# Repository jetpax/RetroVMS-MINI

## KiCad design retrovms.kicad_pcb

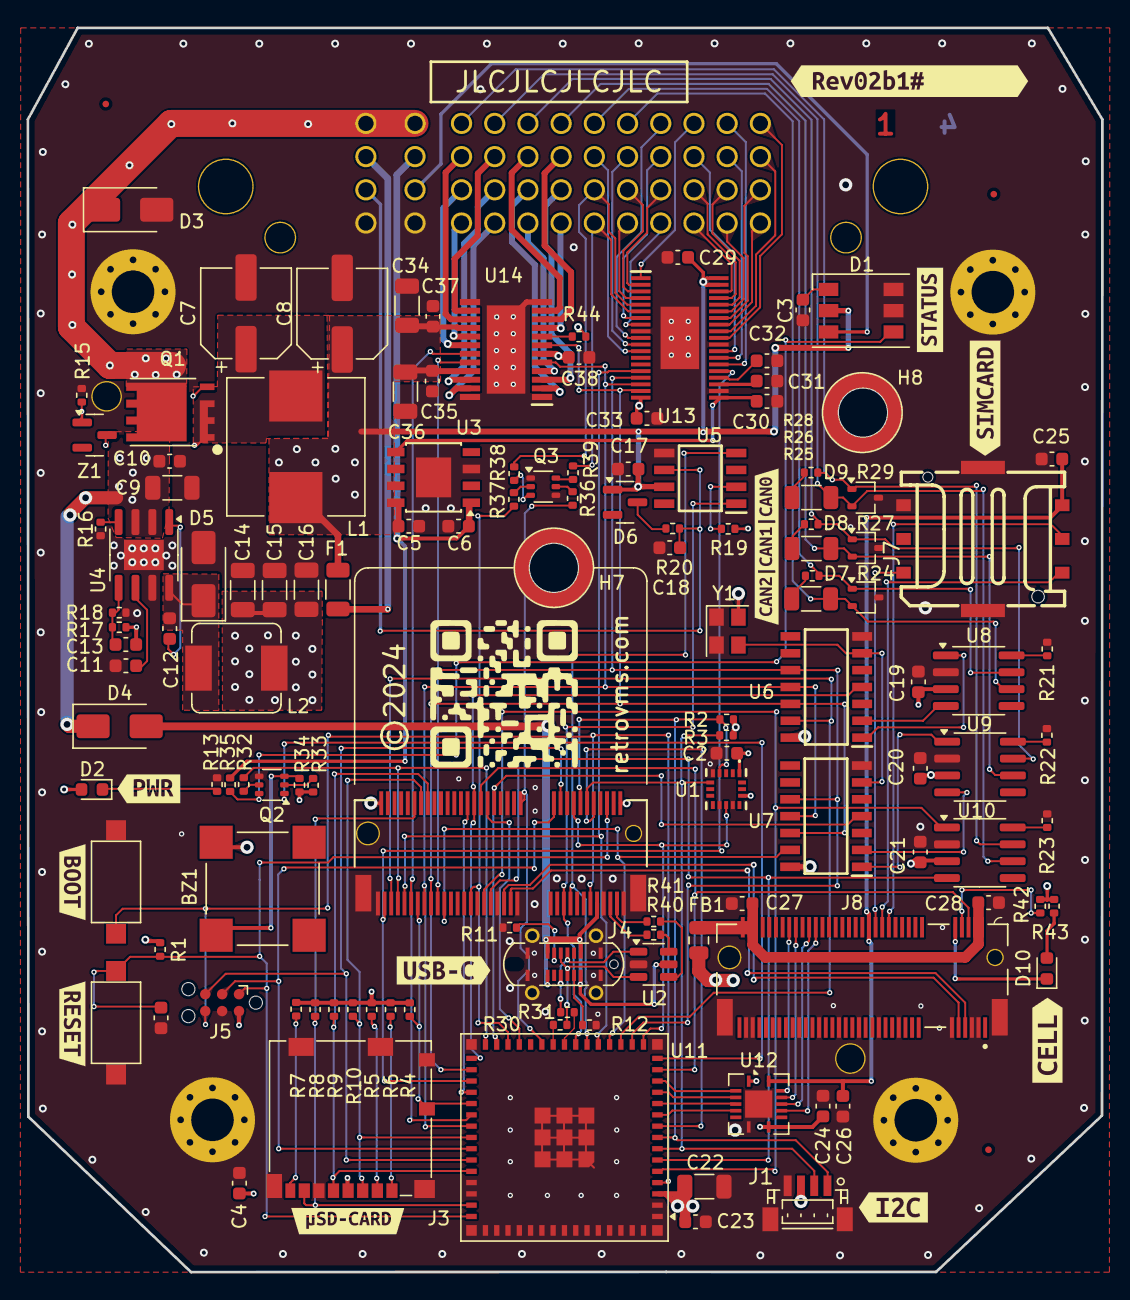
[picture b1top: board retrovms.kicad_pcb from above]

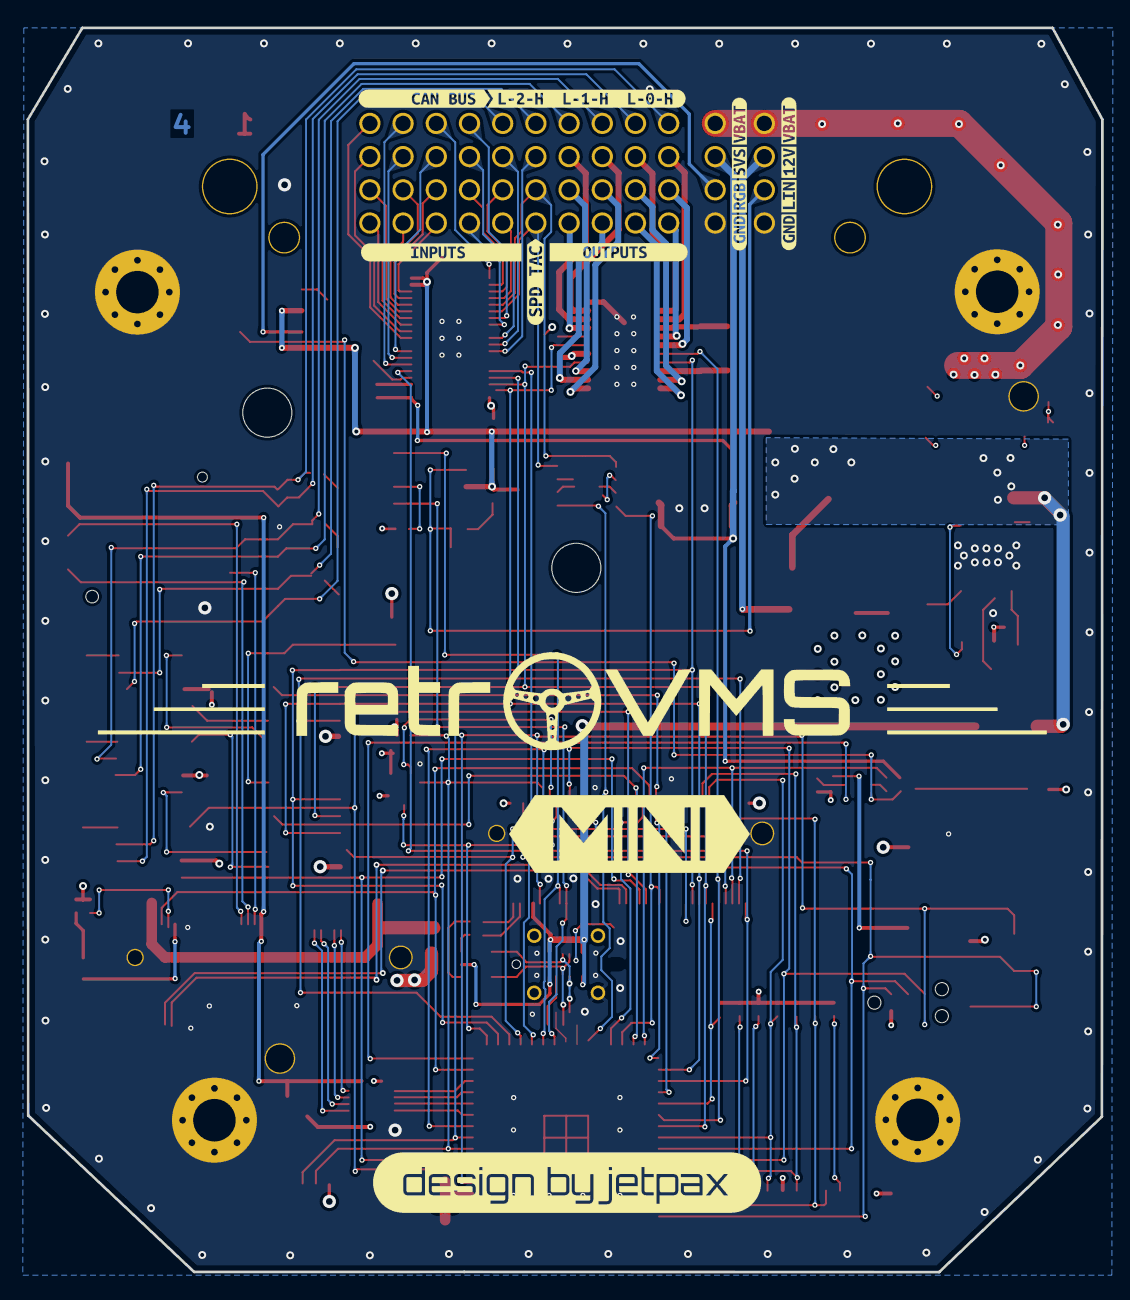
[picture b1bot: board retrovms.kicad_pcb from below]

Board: 4 copper layers, 80.9 x 93.7 mm, 164 parts (15 on the bottom side), 149 nets.

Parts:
BZ1: MLT-8530; PIEZO XDCR_CMT-8503-85B-SMT-TR
C1, C5, C6, C31: 1u; C_0603_1608Metric
C2, C3, C4, C10, C12, C17, C19, C20, C21, C23, C24, C25, C26, C27, C28, C29, C30, C32, C33, C35, C37, C38: 100n; C_0603_1608Metric
C7, C8: 100UF 50V; CP_Elec_6.3x7.7
C9, C34, C36: 4.7u; C_1206_3216Metric
C11: 10n; C_0603_1608Metric
C13, C18: 220p; C_0603_1608Metric
C14, C15, C16, C22: 47u; C_1206_3216Metric
D1: WS2815; LED_WS2812_PLCC6_5.0x5.0mm_P1.6mm
D2, D10: RED_LED; LED_0603_1608Metric
D3: 36V; D_SMA
D4, D5: SS54; D_SMA
D6: BAV70; SOT-23
D7, D8, D9: PESD1CAN-UX; SOT-323_SC-70
F1: 300mA; R_1206_3216Metric
FB1: FerriteBead; C_0805_2012Metric
FID1, FID2, FID3: Fiducial; Fiducial_0.5mm_Mask1mm
H1, H3, H4, H6: MountingHole; MountingHole_3.2mm_M3_Pad_Via
H2, H5: Locating Hole; PTH MountingHole_2.1mm
H7: M2.5 x 1.5mm; WURTH 2.5mm standoff WE_9774025151R
H8: M2.5x3mm; 2.5mmx3mm standoff
J1: JST_PH/STEMMA QT; CONN-SMD_BM04B-SRSS-TB
J2: molex_48pin_500762-0481; Molex_48_MRE
J3: Micro_SD_Card_Det; microSD_HC_Molex_104031-0811
J4: USB_C_Receptacle_USB2.0; USB-C-SMD_GT-USB-7055E
J5: TC2030-IDC_ESP; Tag-Connect_TC2030-IDC-NL_2x03_P1.27mm_Vertical
J6: MicroMod Processor Socket
J7: nanoSIM socket; nanoSIM_SNO-1304-T
J8: M.2 B-key socket; B-Key SIM7600
L1: 1.2u; L_Wuerth_HCI-1050
L2: 1u5 9A 9mΩ; L_Sumida_CDMC6D28_7.25x6.5mm
NT1, NT2: NetTie_2; NetTie-2_SMD_Pad0.15mm
Q1: HY15P03C2; POWERTDFN-8
Q2, Q3: MMDT3904; SOT-363_SC-70-6
R1: 10K; R_0402_1005Metric
R2, R3, R11, R12, R35: 5K1; R_0402_1005Metric
R4, R5, R6, R7, R8, R9, R10, R15, R19, R44: 10k; R_0402_1005Metric
R13, R20, R32, R33, R34, R42: 1K; R_0402_1005Metric
R16: 18k; R_0402_1005Metric
R17: 100k; R_0402_1005Metric
R18: 28k; R_0402_1005Metric
R21, R22, R23, R36, R37, R43: 100K; R_0402_1005Metric
R24, R26, R28, R30, R31, R40, R41: 0R; R_0402_1005Metric
R25, R27, R29: 120R 0.25W; R_1206_3216Metric
R38, R39: 100R; R_0402_1005Metric
SW1, SW2: SW_Push; SW_SPST_CK_RS282G05A3
U1: LIS3DHTR
U2: USBLC6-2SC6; SOT-23-6
U3: TLS115B0EJXUMA1; Infineon_PG-DSO-8-43
U4: LMR14030; SOIC-8-1EP_3.9x4.9mm_P1.27mm_EP2.29x3mm
U5: TLIN2027DRQ1; SOIC127P600X175-8N
U6, U7: MCP2518FDT-E_SL; SOIC127P600X175-14N
U8, U9, U10: SN65HVD230; SOIC-8_3.9x4.9mm_P1.27mm
U11: ESP32-S3-MINI-1-N4R2; ESP32-S2-MINI-1U
U12: TXB0104RGY; Texas_S-PVQFN-N14
U13: TIC10024QDCPRQ1; SOP50P640X120-39N
U14: TLE94112; SOP65P600X170-25N
Y1: 40MHz; Oscillator_SMD_Abracon_ASE-4Pin_3.2x2.5mm
Z1: BZX84C10; SOT-23
kibuzzard-65E9ED88: G***; kibuzzard-65E9ED88
kibuzzard-65E9EDFE: G***; kibuzzard-65E9EDFE
kibuzzard-65E9EE5D: G***; kibuzzard-65E9EE5D
kibuzzard-65E9F7F5: G***; kibuzzard-65E9F7F5
kibuzzard-65E95F8C: G***; kibuzzard-65E95F8C
kibuzzard-65E965A2: G***; kibuzzard-65E965A2
kibuzzard-65E9621C: G***; kibuzzard-65E9621C
kibuzzard-65E96189, kibuzzard-65E96189#2: G***; kibuzzard-65E96189
kibuzzard-65E96414, kibuzzard-65E96414#2: G***; kibuzzard-65E96414
kibuzzard-65E96519: G***; kibuzzard-65E96519
kibuzzard-65E96540: G***; kibuzzard-65E96540
kibuzzard-65EA014A: G***; kibuzzard-65EA014A
kibuzzard-65EA0126: G***; kibuzzard-65EA0126
kibuzzard-65ECBD98: G***; kibuzzard-65ECBD98
kibuzzard-65ECBDEA: G***; kibuzzard-65ECBDEA
kibuzzard-65ECCF8C: G***; kibuzzard-65ECCF8C
kibuzzard-65ECCF47: G***; kibuzzard-65ECCF47
kibuzzard-65ECCF95: G***; kibuzzard-65ECCF95
kibuzzard-65F0D2D4: G***; kibuzzard-65F0D2D4
kibuzzard-65F0D04E: G***; kibuzzard-65F0D04E
kibuzzard-65F0D511: G***; kibuzzard-65F0D511
kibuzzard-65F06A8F: G***; kibuzzard-65F06A8F
kibuzzard-65F084C8: G***; kibuzzard-65F084C8
kibuzzard-65F24715: G***; kibuzzard-65F24715

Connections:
/BUZZ: J6.69 (G7), R32.2, U11.30 (IO48)
/Bus Transceivers/CAN0_H: D9.1 (C1), J2.9, R28.2, U10.7 (CANH)
/Bus Transceivers/CAN0_L: D9.2 (C2), J2.13, R29.2, U10.6 (CANL)
/Bus Transceivers/CAN1_H: D8.1 (C1), J2.17, R26.2, U9.7 (CANH)
/Bus Transceivers/CAN1_L: D8.2 (C2), J2.21, R27.1, U9.6 (CANL)
/Bus Transceivers/CAN2_H: D7.1 (C1), J2.25, R24.2, U8.7 (CANH)
/Bus Transceivers/CAN2_L: D7.2 (C2), J2.29, R25.1, U8.6 (CANL)
/Bus Transceivers/CAN_CLK: U6.6 (OSC1), U7.6 (OSC1), Y1.3 (Out)
/CAN0_RX: J6.41 (CAN_RX), U10.4 (R), U11.6 (IO2)
/CAN0_TX: J6.43 (CAN_TX), U10.1 (D), U11.5 (IO1)
/CAN1_CS: J6.55 (SPI_CS), U7.13 (NCS), U11.19 (IO15)
/CAN1_INT: J6.40 (G0), U7.4 (~INT), U11.29 (IO34)
/CAN2_CS: J6.71 (G6), U6.13 (NCS), U11.18 (IO14)
/CAN2_INT: J6.46 (G3), U6.4 (~INT), U11.31 (IO35)
/D+: J4.A6 (D+), J4.B6 (D+), R31.1, U2.3 (I/O2)
/D-: J4.A7 (D-), J4.B7 (D-), R30.2, U2.1 (I/O1)
/DEV_D+: R41.2, U2.4 (I/O2)
/DEV_D-: R40.2, U2.6 (I/O1)
/FREQ0: J6.47 (PWM1), R37.2, U11.28 (IO33)
/FREQ1: J6.32 (PWM0), R36.2, U11.25 (IO21)
/GD0: J6.10 (D0), U11.9 (IO5)
/I2C_INT: J6.16 (I2C_INT), U1.11 (INT1), U11.16 (IO12)
/INP_CS: J6.67 (G8), U11.20 (IO16), U13.15 (~CS)
/INP_INT: J6.73 (G5), U11.33 (IO37), U13.24 (~INT)
/IPC_CS: J6.42 (G1), U11.27 (IO47)
/IPC_INT: J6.48 (G4), U11.34 (IO38)
/Inputs/IN2: J2.41, U13.25 (IN2)
/Inputs/IN3: J2.42, U13.26 (IN3)
/Inputs/IN4: J2.38, U13.27 (IN4)
/Inputs/IN5: J2.45, U13.29 (IN5)
/Inputs/IN6: J2.46, U13.30 (IN6)
/Inputs/IN7: J2.48, U13.31 (IN7)
/Inputs/IN8: J2.47, U13.32 (IN8)
/Inputs/IN9: J2.44, U13.33 (IN9)
/Inputs/IN10: J2.43, U13.34 (IN10)
/Inputs/IN11: J2.39, U13.35 (IN11)
/Inputs/IN12: J2.40, U13.36 (IN12)
/Inputs/IN13: J2.37, U13.1 (IN13)
/Inputs/IN14: J2.35, U13.2 (IN14)
/Inputs/IN15: J2.31, U13.3 (IN15)
/Inputs/IN16: J2.32, U13.4 (IN16)
/Inputs/IN17: J2.27, NT1.2, U13.5 (IN17)
/Inputs/IN18: J2.28, NT2.2, U13.6 (IN18)
/Inputs/IN19: J2.34, U13.7 (IN19)
/Inputs/IN20: J2.36, U13.8 (IN20)
/Inputs/IN21: J2.33, U13.10 (IN21)
/Inputs/IN22: J2.30, U13.11 (IN22)
/Inputs/IN23: J2.26, U13.12 (IN23)
/LED_STRIP: D1.3 (DOUT), J2.7
/LINBUS: C18.1, J2.3, R20.1, U5.6 (LIN)
/LIN_RX: J6.19 (RX1), U5.1 (RXD), U11.22 (IO18)
/LIN_TX: J6.17 (TX1), U5.4 (TXD), U11.21 (IO17)
/MDM_D+: J6.35 (D+), J8.7
/MDM_D-: J6.37 (D-), J8.9
/MDM_DTR: U11.10 (IO6), U12.5 (A4)
/MDM_PWR: J6.44 (G2), J8.6, U11.14 (IO10)
/MDM_RTS: U11.11 (IO7), U12.4 (A3)
/MDM_RX: U11.12 (IO8), U12.3 (A2)
/MDM_TX: U11.13 (IO9), U12.2 (A1)
/MISO: J6.59 (SPI_SDO), U6.12 (SDO), U7.12 (SDO), U11.32 (IO36), U13.18 (SO), U14.7 (SDO)
/MOSI: J6.61 (SPI_SDI), U6.11 (SDI), U7.11 (SDI), U11.37 (IO41), U13.17 (SI), U14.5 (SDI)
/OUT_CS: J6.65 (G9_ADCD-), U11.36 (IO40), U14.19 (CSN)
/Outputs/OUT1: J2.19 (OUT1), U14.2 (OUT1)
/Outputs/OUT2: J2.16 (OUT2), U14.23 (OUT2)
/Outputs/OUT3: J2.14 (OUT3), U14.14 (OUT3)
/Outputs/OUT4: J2.18 (OUT4), U14.11 (OUT4)
/Outputs/OUT5: J2.23 (OUT5), U14.3 (OUT5)
/Outputs/OUT6: J2.22 (OUT6), U14.10 (OUT6)
/Outputs/OUT7: J2.20 (OUT7), U14.4 (OUT7)
/Outputs/OUT8: J2.15 (OUT8), U14.22 (OUT8)
/Outputs/OUT9: J2.24 (OUT9), U14.9 (OUT9)
/Outputs/OUT10: J2.10 (OUT10), U14.15 (OUT10)
/Outputs/OUT11: J2.12 (OUT11), U14.17 (OUT11)
/Outputs/OUT12: J2.11 (OUT12), U14.18 (OUT12)
/Power/SW: C12.1, D5.1 (K), L2.1, U4.8 (SW)
/Power/V+: C7.1, L1.1, Q1.S, Z1.3 (K)
/Processor/M.2 WWAN Socket/MDM_VBAT: C27.1, C28.1, FB1.2, J8.2, J8.4, J8.70, J8.72, J8.74
/Processor/M.2 WWAN Socket/SIM_CLK: J7.C3 (CLK), J8.32
/Processor/M.2 WWAN Socket/SIM_IO: J7.C7 (I/O), J8.34
/Processor/M.2 WWAN Socket/SIM_RST: J7.C2 (RST), J8.30
/Processor/M.2 WWAN Socket/SIM_VCC: C25.1, C26.1, J7.C1 (VCC), J8.36, U12.14 (VCCB)
/Processor/M.2 WWAN Socket/W_DISABLE: J8.8, R43.2
/Processor/PIEZO: BZ1.N, Q2.3 (C2), R34.1
/Processor/RGB_LED: D1.4 (DIN), Q2.6 (C1), R35.1
/Processor/RMTLED: Q2.1 (E1), U11.15 (IO11)
/Processor/SPEEDO: NT2.1, R39.1
/Processor/TACHO: NT1.1, R38.1
/Processor/USB_D+: R31.2, U11.24 (IO20)
/Processor/USB_D-: R30.1, U11.23 (IO19)
/RXD0: J5.5 (RX), J6.20 (RX2), U11.40 (RXD0)
/SCL: J1.1, J6.14 (I2C_SCL), R2.1, U1.4 (SCL/SCK), U11.8 (IO4)
/SCLK: J6.57 (SPI_SCK), U6.10 (SCK), U7.10 (SCK), U11.17 (IO13), U13.16 (SCLK), U14.20 (SCLK)
/SDA: J1.2, J6.12 (I2C_SDA), R3.1, U1.6 (SDA/SDI), U11.7 (IO3)
/SD_CLK: J3.5 (CLK), J6.60 (SDIO_CLK), R9.2, U11.41 (IO45)
/SD_CMD: J3.3 (CMD), J6.62 (SDIO_CMD), R10.2, U11.38 (IO42)
/SD_DAT0: J3.7 (DAT0), J6.64 (SDIO_DATA0), R8.2, U11.44 (IO46)
/SD_DAT1: J3.8 (DAT1), R7.2
/SD_DAT2: J3.1 (DAT2), R6.2
/SD_DAT3: J3.2 (DAT3/CD), R5.2
/SD_DET: J3.9 (DET), J6.63 (G10_ADCD+), R4.2, U11.35 (IO39)
/TXD0: J5.3 (TX), J6.22 (TX2), U11.39 (TXD0)
/~BOOT: J5.6 (IO0), J6.11 (~BOOT), SW2.2, U11.4 (IO0)
/~RESET: C1.1, J5.1 (EN), J6.6 (~RESET), R1.1, SW1.2, U11.45 (EN)
AREF: C30.1, U3.5 (ADJ), U13.20 (CAP_A)
GND: C1.2, C2.2, C3.2, C4.2, C5.2, C6.2, C7.2, C8.2, C9.2, C10.2, C11.2, C14.2, C15.2, C16.2, C17.2, C18.2, C19.2, C20.2, C21.2, C22.2, C23.2, C24.2, C25.2, C26.2, C27.2, C28.2, C29.2, C30.2, C31.2, C32.2, C33.2, C34.2, C35.2, C36.2, C37.2, C38.2, D1.5 (GND), D1.6 (BIN), D3.2 (A2), D5.2 (A), D7.3 (C3), D8.3 (C3), D9.3 (C3), H1.1, H2.1, H3.1, H4.1, H5.1, H6.1, H7.1, H8.1, J1.4, J1.MP (MountPin), J2.4, J2.8, J3.6 (VSS), J3.10 (DET_A), J3.11 (SHIELD), J4.A1 (GND), J4.A12 (GND), J4.B1 (GND), J4.B12 (GND), J4.S1 (SHIELD), J5.4 (GND), J6.1 (GND), J6.7 (GND), J6.33 (GND), J6.36 (GND), J6.39 (GND), J6.45 (GND), J6.75 (GND), J6.H1 (HOLE), J6.H2 (HOLE), J6.S1 (SHIELD), J6.S2 (SHIELD), J7.C5 (GND), J7.S1 (GND), J8.3, J8.5, J8.11, J8.27, J8.33, J8.39, J8.45, J8.51, J8.57, J8.71, J8.73, J8.H1 (HOLE), J8.H2 (HOLE), J8.S1 (SHIELD), J8.S2 (SHIELD), Q2.4 (E2), Q3.1 (E1), Q3.4 (E2), R11.1, R12.1, R13.1, R15.2, R16.2, R18.2, R21.1, R22.1, R23.1, SW1.1, SW2.1, U1.5 (GND), U1.10 (RES), U1.12 (GND), U2.2 (GND), U3.3 (GND), U3.9 (GND), U4.7 (GND), U4.9 (GND), U5.5 (GND), U6.7 (VSS), U7.7 (VSS), U8.2 (GND), U9.2 (GND), U10.2 (GND), U11.1 (GND), U11.2 (GND), U11.42 (GND), U11.43 (GND), U11.46 (GND), U11.47 (GND), U11.48 (GND), U11.49 (GND), U11.50 (GND), U11.51 (GND), U11.52 (GND), U11.53 (GND), U11.54 (GND), U11.55 (GND), U11.56 (GND), U11.57 (GND), U11.58 (GND), U11.59 (GND), U11.60 (GND), U11.61 (GND), U11.62 (GND), U11.63 (GND), U11.64 (GND), U11.65 (GND), U12.7 (GND), U12.15 (Pad), U13.9 (AGND), U13.21 (RESET), U13.28 (DGND), U13.39 (EP), U14.1 (GND), U14.12 (GND), U14.13 (GND), U14.24 (GND), U14.25 (EDP), Y1.1 (Standby), Y1.2 (GND)
unnamed: C3.1, D1.1 (VCC)
unnamed: D2.1 (K), R13.2
unnamed: D6.3 (K), R20.2
unnamed: D10.2 (A), R42.2
unnamed: D10.1 (K), J8.10
unnamed: J4.A5 (CC1), R12.2
unnamed: J4.B5 (CC2), R11.2
unnamed: J6.3 (D+), R41.1
unnamed: J6.5 (D-), R40.1
unnamed: Q2.2 (B1), R33.1
unnamed: Q2.5 (B2), R32.1
unnamed: Q3.2 (B1), R37.1
unnamed: Q3.6 (C1), R39.2
unnamed: Q3.5 (B2), R36.1
unnamed: Q3.3 (C2), R38.2
unnamed: R24.1, R25.2
unnamed: R26.1, R27.2
unnamed: R28.1, R29.1
unnamed: C12.2, U4.1 (BOOT)
unnamed: C13.2, R17.1, R18.1, U4.5 (FB)
unnamed: R16.1, U4.4 (RT)
unnamed: C11.1, U4.6 (SS)
unnamed: R19.2, U5.2 (EN)
unnamed: U6.2 (RXCAN), U8.4 (R)
unnamed: U6.1 (TXCAN), U8.1 (D)
unnamed: U7.2 (RXCAN), U9.4 (R)
unnamed: U7.1 (TXCAN), U9.1 (D)
unnamed: R21.2, U8.8 (Rs)
unnamed: R22.2, U9.8 (Rs)
unnamed: R23.2, U10.8 (Rs)
unnamed: J8.60, U12.13 (B1)
unnamed: J8.58, U12.12 (B2)
unnamed: J8.54, U12.11 (B3)
unnamed: J8.52, U12.10 (B4)
unnamed: C32.1, U13.23 (CAP_D)
unnamed: C31.1, U13.22 (CAP_PRE)
unnamed: R44.2, U14.8 (EN)
unnamed: Q1.G, R15.1, Z1.1 (A)
SENSOR_5V: C6.1, J2.6, R35.2, U3.1 (OUT)
SENSOR_12V: F1.2, J2.2
VBAT: D3.1 (A1), J2.1, J2.5, Q1.D
VBUS: D4.2 (A), J4.A4 (VBUS), J4.A9 (VBUS), J4.B4 (VBUS), J4.B9 (VBUS), J6.9 (VUSB), U2.5 (VBUS)
VDD: BZ1.P, C2.1, C4.1, C13.1, C14.1, C15.1, C16.1, C19.1, C20.1, C21.1, C22.1, C23.1, C24.1, C33.1, C38.1, D2.2 (A), FB1.1, J1.3, J3.4 (VDD), J5.2 (VDD), J6.2 (3.3V), J6.74 (3.3V), L2.2, R1.2, R2.2, R3.2, R4.1, R5.1, R6.1, R7.1, R8.1, R9.1, R10.1, R17.2, R19.1, R33.2, R34.2, R42.1, R43.1, R44.1, U1.1 (VDDIO), U1.14 (VDD), U6.14 (VDD), U7.14 (VDD), U8.3 (VCC), U9.3 (VCC), U10.3 (VCC), U11.3 (3V3), U12.1 (VCCA), U12.8 (OE), U13.19 (VDD), U14.6 (VDD), Y1.4 (VDD)
VPROT: C5.1, C8.1, C9.1, C10.1, C17.1, C29.1, C34.1, C35.1, C36.1, C37.1, D1.2 (VDD), D4.1 (K), D6.1 (A), F1.1, L1.2, U3.7 (EN), U3.8 (IN), U4.2 (VIN), U4.3 (EN), U5.7 (VSUP), U13.37 (VS_1), U13.38 (VS_2), U14.16 (VS1), U14.21 (VS2)

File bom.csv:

Designator,Footprint,Quantity,Value,LCSC Part #
BZ1,PIEZO XDCR_CMT-8503-85B-SMT-TR,1,MLT-8530,C94599
"C1, C31, C5, C6",0603,4,1u,C15849
"C10, C12, C17, C19, C2, C20, C21, C23, C24, C25, C26, C27, C28, C29, C3, C30, C32, C33, C35, C37, C38, C4",0603,22,100n,C14663
C11,0603,1,10n,C57112
"C13, C18",0603,2,220p,C1603
"C14, C15, C16, C22",1206,4,47u,C96123
"C34, C36, C9",1206,3,4.7u,C29823
"C7, C8",CP_Elec_6.3x7.7,2,100UF 50V,C7461243
D1,LED_WS2812_PLCC6_5.0x5.0mm_P1.6mm,1,WS2815,C4154879
"D10, D2",0603,2,RED_LED,C965799
D3,D_SMA,1,36V,C83266
"D4, D5",D_SMA,2,SS54,C22452
D6,SOT-23,1,BAV70,C68978
"D7, D8, D9",SOT-323_SC-70,3,PESD1CAN-UX,C907839
F1,1206,1,300mA,C207035
FB1,0805,1,FerriteBead,C16903
H7,WURTH 2.5mm standoff WE_9774025151R,1,M2.5 x 1.5mm,C2915629
H8,2.5mmx3mm standoff,1,M2.5x3mm,C2916380
J1,CONN-SMD_BM04B-SRSS-TB,1,JST_PH/STEMMA QT,C160390
J3,microSD_HC_Molex_104031-0811,1,Micro_SD_Card_Det,C585350
J4,USB-C-SMD_GT-USB-7055E,1,USB_C_Receptacle_USB2.0,C7450622
J6,MicroMod Processor Socket,1,MicroMod Processor Socket,C841649
J7,nanoSIM_SNO-1304-T,1,nanoSIM socket,C428460
J8,B-Key SIM7600,1,M.2 B-key socket,C2761526
L1,L_Wuerth_HCI-1050,1,1.2u,C149536
L2,L_Sumida_CDMC6D28_7.25x6.5mm,1, 1u5 9A 9mΩ,C216162
Q1,POWERTDFN-8,1,HY15P03C2,C123687
"Q2, Q3",SOT-363_SC-70-6,2,MMDT3904,C3018510
"R1, R10, R15, R19, R4, R44, R5, R6, R7, R8, R9",0402,11,10K,C25744
"R11, R12, R2, R3, R35",0402,5,5K1,C25905
"R13, R20, R32, R33, R34, R42",0402,6,1K,C11702
R16,0402,1,18k,C25762
"R17, R21, R22, R23, R36, R37, R43",0402,7,100k,C25741
R18,0402,1,28k,C25772
"R24, R26, R28, R30, R31",0402,5,0R,C17168
"R25, R27, R29",1206,3,120R 0.25W,C17909
"R38, R39",0402,2,100R,C25076
"SW1, SW2",SW_SPST_CK_RS282G05A3,2,SW_Push,C398054
U1,LIS3DHTR,1,LIS3DHTR,C15134
"U10, U8, U9",SOIC-8_3.9x4.9mm_P1.27mm,3,SN65HVD230,C12084
U11,ESP32-S2-MINI-1U,1,ESP32-S3-MINI-1-N4R2,C3013941 
U12,Texas_S-PVQFN-N14,1,TXB0104RGY, C400708
U13,SOP50P640X120-39N,1,TIC10024QDCPRQ1,C2652907
U14,SOP65P600X170-25N,1,TLE94112,C2680272 
U2,SOT-23-6,1,USBLC6-2SC6,C7519
U3,Infineon_PG-DSO-8-43,1,TLS115B0EJXUMA1,C3743696
U4,SOIC-8-1EP_3.9x4.9mm_P1.27mm_EP2.29x3mm,1,LMR14030,C182078
U5,SOIC127P600X175-8N,1,TLIN2027DRQ1,C2862879
"U6, U7",SOIC127P600X175-14N,2,MCP2518FDT-E_SL,C626759
Y1,Oscillator_SMD_Abracon_ASE-4Pin_3.2x2.5mm,1,40MHz,C5203551
Z1,SOT-23,1,BZX84C10,C235751

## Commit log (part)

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2024-04-20 init
2024-04-20 update wks

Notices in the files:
retrovms.kicad_pcb:
©2024
